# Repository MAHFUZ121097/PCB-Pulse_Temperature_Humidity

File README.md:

# Pulse Oximeter and Temperature-Humidity Sensor PCB

## Overview

This repository contains the design and firmware for a custom Printed Circuit Board (PCB) that integrates both a pulse oximeter and a temperature-humidity sensor. This PCB is designed to monitor vital physiological data, making it suitable for health monitoring and IoT applications.

### PCB Image

### Key Components:
- **Pulse Oximeter IC**: MAX30101
- **Temperature-Humidity IC**: Si7021
- **Voltage Regulators**: 5V, 1.8V

The PCB design ensures efficient power regulation and integrates sensor functionality in a compact, easy-to-use form.

## Components Description

### Pulse Oximeter (MAX30101)
- The MAX30101 is an integrated pulse oximetry and heart-rate monitor IC. It uses two LEDs (red and infrared) and a photodetector to measure blood oxygen saturation and heart rate.

### Temperature-Humidity Sensor (Si7021)
- The Si7021 is a digital temperature and humidity sensor with high accuracy and low power consumption. It provides environmental data that can be used to monitor air quality or adjust for environmental conditions in health monitoring applications.

### Voltage Regulators
- The PCB includes voltage regulation circuits for powering the sensors and components:
  - **5V Regulator**: For high logic level for MAX30101 operation
  - **1.8V Regulator**: For low logic level for MAX30101 operation

## Features
- **Compact design** that integrates both sensors on a single PCB.
- **Accurate physiological monitoring** using the MAX30100 pulse oximeter and the Si7021 temperature-humidity sensor.
- **Efficient power management** with onboard voltage regulators (5V and 1.8V).

## PCB Specifications
- **Design environment**: KiCad EDA 6.0.10
- **Dimensions**: 30 mm X 22 mm
- **Operating Voltage**: ~ 3V.
- **Interfaces**: I2C communication pins for data exchange between the sensors and microcontroller.

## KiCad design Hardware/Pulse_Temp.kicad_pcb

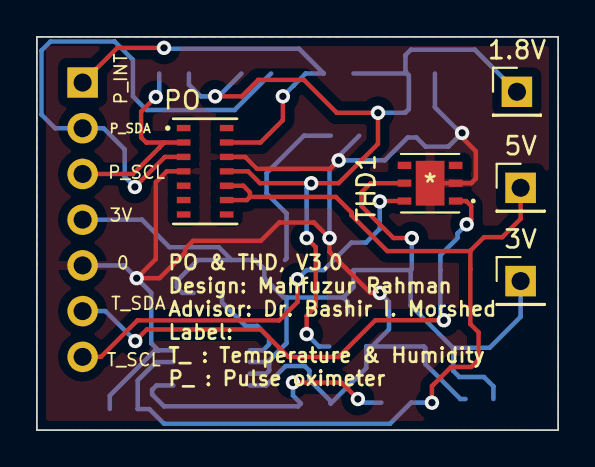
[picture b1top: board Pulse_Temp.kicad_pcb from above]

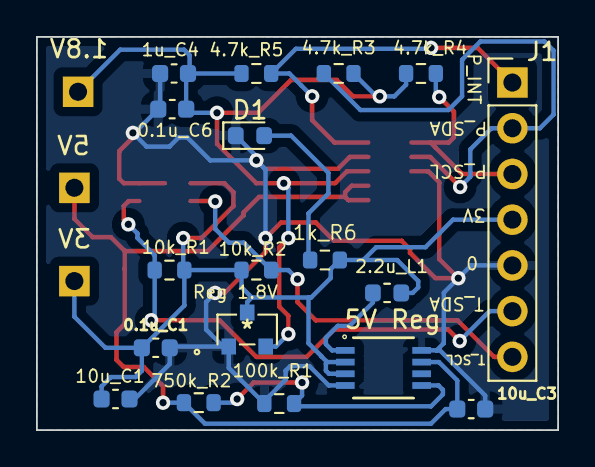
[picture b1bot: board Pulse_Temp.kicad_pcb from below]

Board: 2 copper layers, 29.0 x 21.8 mm, 23 parts (18 on the bottom side), 12 nets.

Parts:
0.1u_C1, 0.1u_C6: 0.1u; C_0603_1608Metric
1.8V, 3V, 5V: TestPoint; PinHeader_1x01_P2.54mm_Vertical
1k_R6: 1k; R_0603_1608Metric
1u_C4: 1u; C_0603_1608Metric
2.2u_L1: 2.2u; L_0603_1608Metric
4.7k_R3, 4.7k_R4, 4.7k_R5: 4.7k; R_0603_1608Metric
5V Reg: PAM2401SCADJ; MSOP8_DIO
10k_R1, 10k_R2: 10k; R_0603_1608Metric
10u_C1, 10u_C3: 10u; C_0603_1608Metric
100k_R1: 100k; R_0603_1608Metric
750k_R2: 750k; R_0603_1608Metric
D1: LED; LED_0603_1608Metric
J1: Conn_01x07; PinHeader_1x07_P2.54mm_Vertical
PO: MAX30101EFD+T; 21-1048F_F143A5&plus_1_MXM
Reg 1.8V: AP2120N-1.8TRG1
THD1: SI7021-A20-GM1R

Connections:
0: 0.1u_C1.2, 0.1u_C6.1, 1u_C4.2, 5V Reg.4 (AGND), 5V Reg.8 (PGND), 10u_C1.2, 10u_C3.2, 100k_R1.2, D1.1 (K), J1.5, PO.4 (PGND), PO.12 (GND), Reg 1.8V.1 (GND), THD1.2 (GND), THD1.7 (EPAD)
/1.8V: 0.1u_C6.2, 1.8V.1, 1u_C4.1, 4.7k_R3.2, 4.7k_R4.1, 4.7k_R5.2, PO.11 (VDD), Reg 1.8V.2 (VOUT)
/3V: 0.1u_C1.1, 1k_R6.1, 2.2u_L1.1, 3V.1, 5V Reg.2 (EN), 5V Reg.3 (VIN), 10k_R1.1, 10k_R2.2, 10u_C1.1, J1.4, Reg 1.8V.3 (VIN), THD1.5 (VDD)
/5V: 5V.1, 5V Reg.7 (OUT), 10u_C3.1, 750k_R2.2, PO.9 (VLED+), PO.10 (VLED+)
/PO_INT: 4.7k_R5.1, J1.1, PO.13 (*INT)
/PO_SCL: 4.7k_R4.2, J1.3, PO.2 (SCL)
/PO_SDA: 4.7k_R3.1, J1.2, PO.3 (SDA)
/THD_SCL: 10k_R2.1, J1.7, THD1.6 (SCL)
/THD_SDA: 10k_R1.2, J1.6, THD1.1 (SDA)
unnamed: 1k_R6.2, D1.2 (A)
unnamed: 2.2u_L1.2, 5V Reg.1 (LX)
unnamed: 5V Reg.5 (FB), 100k_R1.1, 750k_R2.1

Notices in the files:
parts and their libraries:
Copyright 2021 Accelerated Designs. All rights reserved.
